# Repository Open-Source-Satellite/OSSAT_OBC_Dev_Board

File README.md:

# Open Source Satellite Development On Board Computer

## Contents
- [Background](#background)
- [Introduction to the OBC Development Board](#Introduction-to-the-OBC-Development-Board)
- [OBC Development Board Manual](#OBC-Development-Board-Manual)
- [Running the OSSAT OBC Application](#running-the-ossat-obc-application)

## Background
The key drivers for the Open Source Satellite (OSSAT) are to improve the affordability, accessibility and
sustainability of space; to address the market need for an improvement in the
price:performance point of small satellites; to stimulate the next wave of disruption
in the small satellite industry; and to enable the development of new missions,
applications and services.

Small satellites initiated the initial market
disruption by leveraging COTS parts and
processes, but it appears that the unit cost
per spacecraft cannot be reduced much
further.  
CubeSats have been critical in recent years for
lowering the barriers to entry, however they
appear to be unable to provide sufficient
robustness and mission enabling capability to
support more demanding missions.  
The goal is to develop OSSAT to fill this gap and deliver microsatellite-class
performance for a CubeSat price, even when manufacturing in low volumes. The
aim is to increase the level of integration and robustness over subsequent missions
in order to develop a single platform that is affordable for use in vLEO (very Low
Earth Orbit), LEO (Low Earth Orbit), GEO (Geosynchronous Equatorial Orbit), Lunar and
interplanetary missions.  
OSSAT will be a performant and flexible
system that KISPE Space will be able to use to implement some of its own
commercial missions; however, simply using it for KISPE Space missions will not
result in the desired increase in accessibility to the design, nor stimulate the
market.  
Making the OSSAT design open source will maximise access and achieve the wider aims of the
Programme.  

## Introduction to the OBC Development Board
### Overview
The OSSAT OBC Development board provides a convenient hardware platform that collaborators can use, to develop satellite firmware.
The board is based upon the STM32 microcontroller and includes various interfaces for connection to other satellite sub-systems. 
The board includes an STLink programmer/debugger interface to facilitate firmware development and debugging activities.
The design shares several attributes with a sister board that is being developed for a space application.
Figure 1 shows a view of the board.

Figure 1:  View of the Board
<br/>
<br/>
### Features
- STM32 Microcontroller (STM32H753ZIT)
- SRAM 4Mx16bit (8Mx8bit) CMOS Static RAM
- STLink Programming and Debug interface (with UART)
- 2x CAN Bus channels (with local 120R termination), with D-Sub (9 way sockets)
- 2x UART interface
- 8x Thermistor interface (10K Negative Temperature Coefficient)
- 31x General purpose I/O lines
- Local 3V3 regulator, operating from USB supply, via Micro-USB connector
- MCU Reset Button
- 2x push-buttons for test use
- 3x status LEDs for test use
- 2x power status LEDs
- Real-time clock

### Technical Details
#### Board Overview
Figure 2 below shows a view of the fully assembled board. There are no components on the reverse side.

Figure 2:  View of Assembled Board
<br/>   
<br/> 
The block diagram for the Schematic is shown in Figure 3.

Figure 3:  Schematic Block Diagram
<br/>   
<br/> 
#### STM32 Microcontroller (STM32H753ZIT)
The STM32 MCU includes a broad set of internal features, some of which are highlighted below:
- 32-bit Arm®-M7 core
- 2Mbyte onboard Flash
- 1Mbyte RAM
- Flexible Memory controller
- Power management
- Watchdog
- Multiple communication peripherals, including CAN, I2C, SPI, UART
- ADC
- Timers and RTC
- Large number of I/O ports
- STLink / JTAG compatibility

Full details of the MCU are available from the manufacturers data sheet and reference manual, available from the STM web site. Refer to:
- DS12117: STM32H753xl Datasheet (32-bit Arm® Cortex®-M7 480MHz MCUs, 2MB Flash, 1MB RAM, 46 com. and analogue interfaces, crypto)
- RM0433: Reference manual, STM32H742, STM32H743/753 and STM32H750 Value line advanced Arm®-based 32-bit MCUs

### Related Documents
A list of documents related to this board is provided in the Manual and is listed here. This includes diagrams, design source files, manufacturing and & test information and test firmware.
- [KS-SCH-01466 (.PDF)](https://github.com/Open-Source-Satellite/OSSAT_OBC_Dev_Board/blob/main/OSSAT%20OBC%20Dev%20Board%20Drawings/KS-SCH-01466-01%20OSSAT%20OBC%20Dev%20Board%20Schematic.pdf) OSSAT OBC Development Board Schematic (Schematic diagram)
- [KS-SCH-01466 (.sch)](https://github.com/Open-Source-Satellite/OSSAT_OBC_Dev_Board/blob/main/OSSAT%20OBC%20Dev%20Board%20Drawings/CAD%20Source%20Files/KS-SCH-01466-01%20OSSAT%20OBC%20Dev%20Board%20Schematic.sch) OSSAT OBC Development Board Schematic (Fusion 360 schematic source file, in ‘Eagle’ format)
- [KS-SCH-01466 (.lbr)](https://github.com/Open-Source-Satellite/OSSAT_OBC_Dev_Board/blob/main/OSSAT%20OBC%20Dev%20Board%20Drawings/CAD%20Source%20Files/KS-SCH-01466-01%20OSSAT_OBC_Dev_Board_Library.lbr) OSSAT OBC Dev board library (Fusion 360 Library file in ‘Eagle’ format, for parts used in the design)
- [KS-SCH-01466 (.xlsx)](https://github.com/Open-Source-Satellite/OSSAT_OBC_Dev_Board/blob/main/OSSAT%20OBC%20Dev%20Board%20Drawings/KS-SCH-01466-01%20OSSAT%20OBC%20Dev%20Brd%20BOM%20with%20Mfr%20Data.xlsx) OSSAT OBC Dev Board BOM with manufacturer data (Bill of materials for the board assembly)
- [KS-BRD-01467 (.brd)](https://github.com/Open-Source-Satellite/OSSAT_OBC_Dev_Board/blob/main/OSSAT%20OBC%20Dev%20Board%20Drawings/CAD%20Source%20Files/KS-SCH-01467%20OSSAT%20OBC%20Dev%20Board%20PCB.brd) OSSAT OBC Development Board PCB (Fusion 360 PCB source file in ‘Eagle’ format)
- [KS-BRD-01467 (.zip)](https://github.com/Open-Source-Satellite/OSSAT_OBC_Dev_Board/blob/main/OSSAT%20OBC%20Dev%20Board%20Drawings/Gerber%20Files/KS-BRD-01467-02%20OSSAT%20Sw%20Dev%20Board%20PCB_2022-12-08.zip) OSSAT OBC Dev Board PCB Manufacturing files	(Gerber file set and PnP file)
- [KS-BRD-01467 (.docx)](https://github.com/Open-Source-Satellite/OSSAT_OBC_Dev_Board/blob/main/OSSAT%20OBC%20Dev%20Board%20Drawings/KS-BRD-01467-02%20OSSAT%20OBC%20Dev%20board%20PCB%20Layer%20Stackup.docx) OSSAT OBC Dev Board Layer Stack-up (Defines the layer stack and pcb materials / thicknesses for the board)
- [KS-DOC-01526 (.docx)](https://github.com/Open-Source-Satellite/OSSAT_OBC_Dev_Board/blob/main/OSSAT%20OBC%20Dev%20Board%20Drawings/KS-DOC-01526-02%20OSSAT%20OBC%20Dev%20Board%20Verification%20Procedure.docx) OSSAT OBC Dev Board Verification Procedure	(Used to confirm board function after build)
- [KS-DOC-01529 (.docx)](https://github.com/Open-Source-Satellite/OSSAT_OBC_Dev_Board/blob/main/OSSAT%20OBC%20Dev%20Board%20Drawings/KS-DOC-01529-01%20OSSAT%20OBC%20Dev%20Board%20Build%20Document.docx) OSSAT OBC Dev Board Build Document (Build process control document)
- [KS-SOF-01541 (software)](https://github.com/Open-Source-Satellite/OSSAT_OBC_Dev_Board/releases/tag/KS-SOF-01541-01) Software to support h/w test of the OSSAT OBC dev board	(Test Software)

## OBC Development Board Manual
Document [KS-DOC-01543 is the manual](https://github.com/Open-Source-Satellite/OSSAT_OBC_Dev_Board/blob/main/KS-DOC%2001543-01%20OSSAT%20OBC%20Dev%20Board%20Manual.docx) for the board. It covers:
- Board features
- Technical details
- Building the board
- Testing the board
- Using the board

## Running the OSSAT OBC Application
Within one year of the first launch of the OSSAT, the OSSAT OBC Application software will become open source. In the interim time, in order to develop/build and run the OSSAT OBC Application, you'll need to become an OSSAT collaborator ([Click Here](https://www.opensourcesatellite.org/register/)).
If you are an OSSAT collaborator, that's great... Click [here](/OBC_CODE_README.md) to find out how to run the OSSAT OBC Application on this development board.

## Licenses
All information in this repository is licensed Open Source through the Creative Commons license:

## Get Involved
If you wish to contribute directly to the development of OSSAT, have a look at the existing Github issues and register [here](https://www.opensourcesatellite.org/register/).

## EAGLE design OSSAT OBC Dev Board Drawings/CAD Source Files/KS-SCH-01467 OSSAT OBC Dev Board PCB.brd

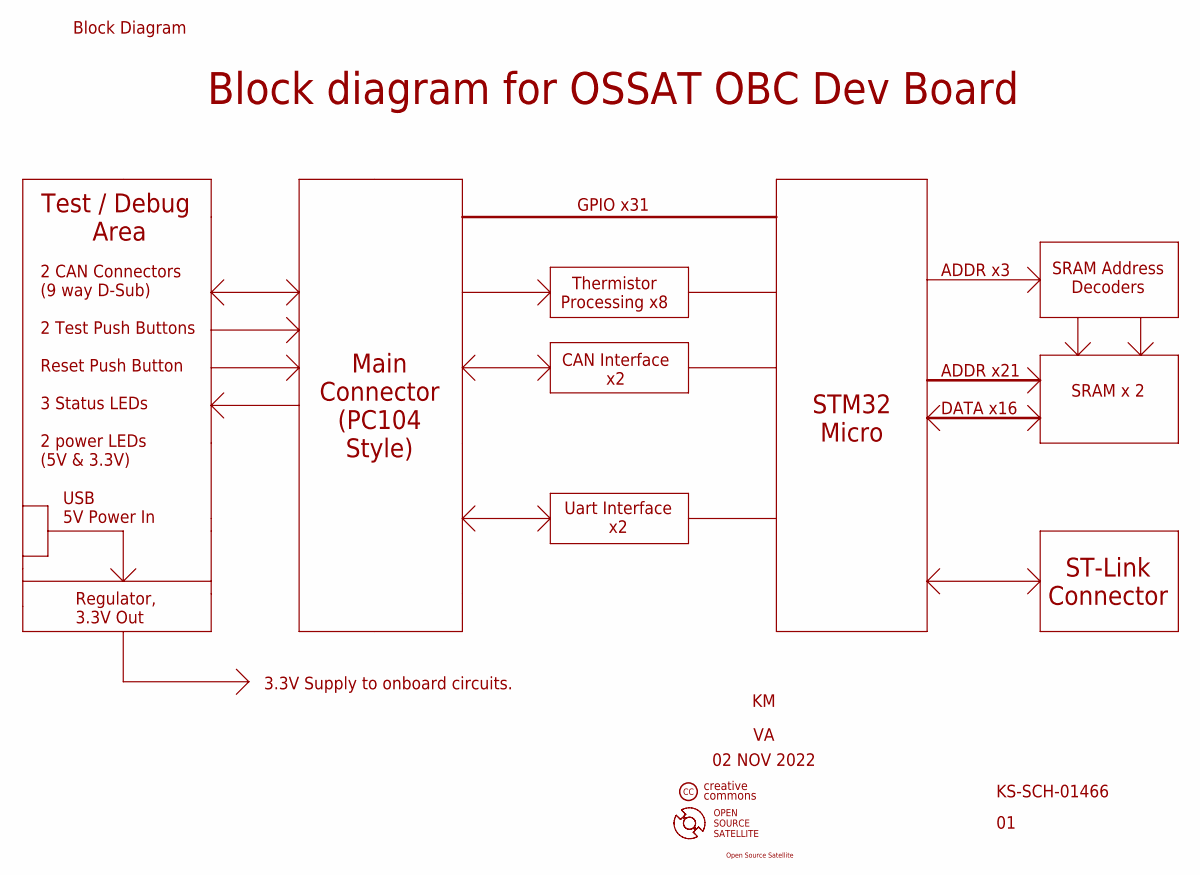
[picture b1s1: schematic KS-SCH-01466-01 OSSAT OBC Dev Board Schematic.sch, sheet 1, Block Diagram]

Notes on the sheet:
Block Diagram
Main Connector (PC104 Style)
STM32 Micro
Thermistor Processing x8
CAN Interface x2
Uart Interface x2
KS-SCH-01466
SRAM Address Decoders
SRAM x 2
ST-Link Connector
ADDR x21
DATA x16
ADDR x3
GPIO x31
Block diagram for OSSAT OBC Dev Board
02 NOV 2022
Test / Debug Area
Regulator, 3.3V Out
USB 5V Power In
3.3V Supply to onboard circuits.
2 CAN Connectors (9 way D-Sub) 2 Test Push Buttons Reset Push Button 3 Status LEDs 2 power LEDs (5V & 3.3V)
OPEN SOURCE SATELLITE
creative commons
Open Source Satellite

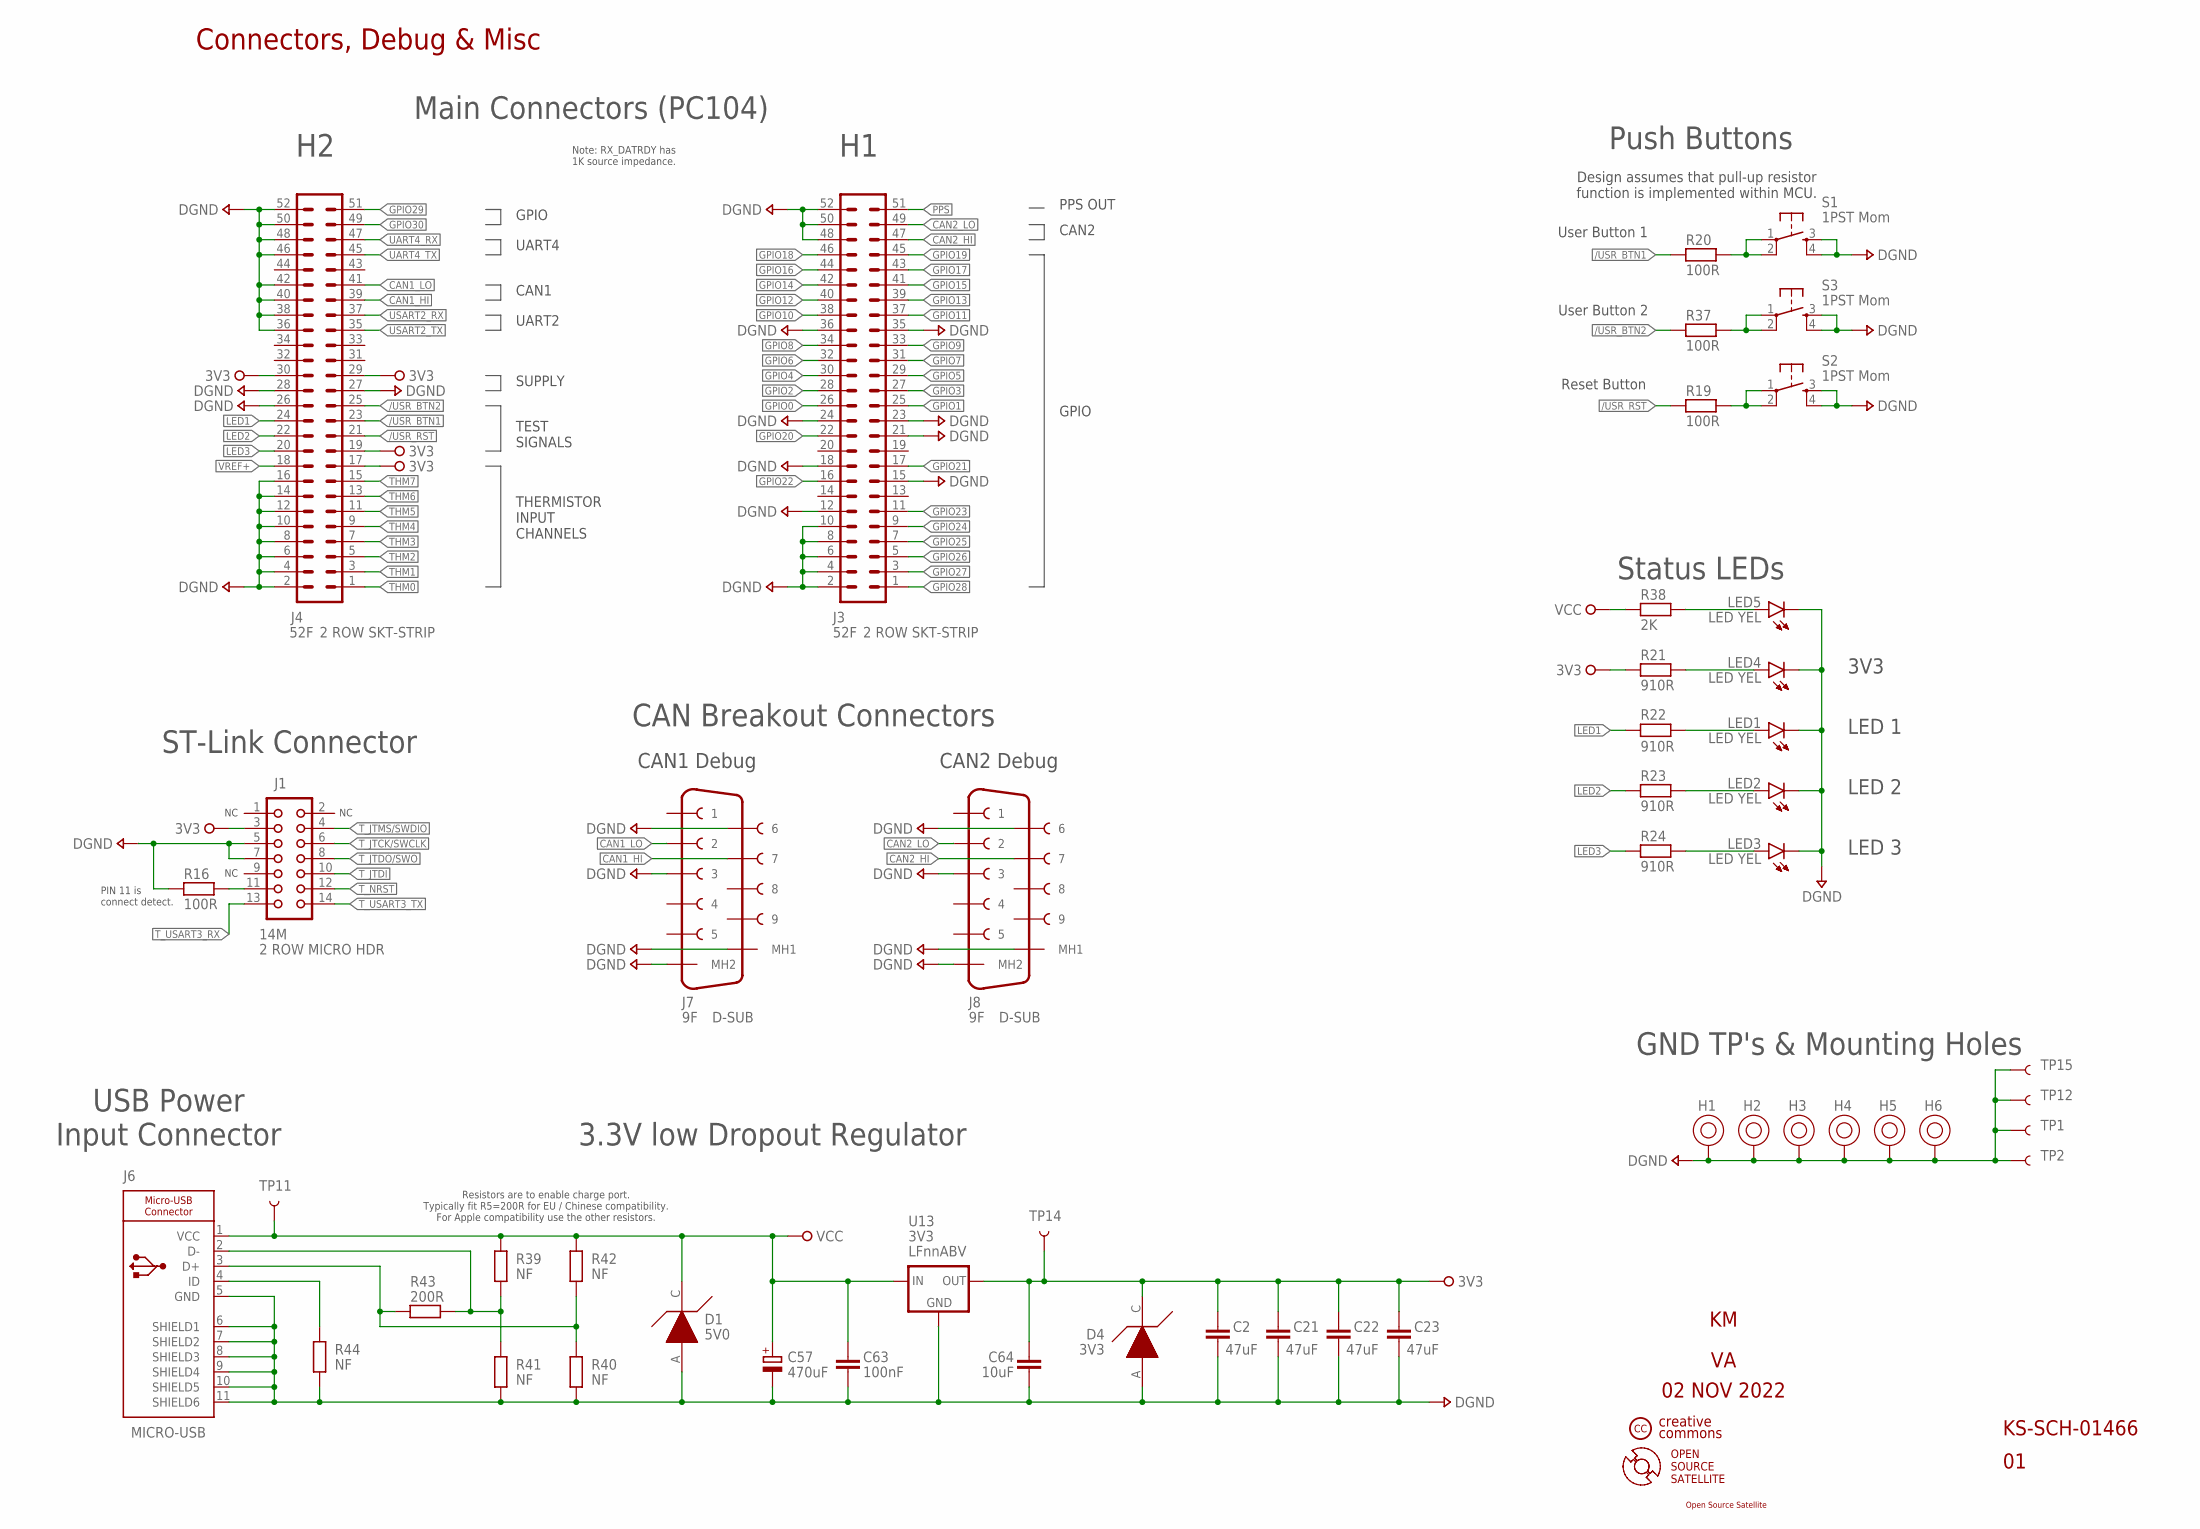
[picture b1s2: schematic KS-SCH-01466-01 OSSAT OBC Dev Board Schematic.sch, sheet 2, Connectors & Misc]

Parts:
C2, C21, C22, C23: 47uF; CAPC3225X135_1210
C57: 470uF; CAP_ELECT_RADIAL_D10_H12.5_P5
C63: 100nF; CAP_CHIP_0805
C64: 10uF; CAPC3225X135_1210
D1: 5V0; SOD323
D4: 3V3; SOD323
H1, H2, H3, H4, H5, H6: NF; HOLE-PTH-3.2-6.35
J1: 14M; HDRV14W41P127_2X7_FTSH
J3, J4: 52F; HDRVR52W64P254_2X26_6655X495X1105B
J6: CNRP105A_MICRO-USB_90DEG; CON_MICRO_USB_FEMALE
J7, J8: 9F; LD09S24A4GV00LF
LED1, LED2, LED3, LED4, LED5: OPTL102A_LED_YELLOW_0805_120DEG; LED_CHIP_0805
R16, R19, R20, R37: 100R; RES_CHIP_0805
R21, R22, R23, R24: 910R; RES_CHIP_0805
R38: 2K; RES_CHIP_0805
R39, R40, R41, R42, R44: NF; RES_CHIP_0805
R43: 200R; RES_CHIP_0805
S1, S2, S3: SWTA100A_1PST_SMD_MOMENTARY_PUSH-BUTTON; TACTILE_SWITCH_SMD_5.2MM
TP1, TP2, TP11, TP12, TP14, TP15: NF; TP-40TH
U13: 3V3; TO220L1A

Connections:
3V3: C2.1, C21.1, C22.1, C23.1, C64.1, D4.C (K), J1.3, J4.17, J4.19, J4.29, J4.30, R21.1, TP14.P$1, U13.3 (OUT); also elsewhere on the board
/USR_BTN1: J4.23, R20.2; also elsewhere on the board
/USR_BTN2: J4.25, R37.2; also elsewhere on the board
/USR_RST: J4.21, R19.2; also elsewhere on the board
CAN1_HI: J4.39, J7.7; also elsewhere on the board
CAN1_LO: J4.41, J7.2; also elsewhere on the board
CAN2_HI: J3.47, J8.7; also elsewhere on the board
CAN2_LO: J3.49, J8.2; also elsewhere on the board
DGND: C2.2, C21.2, C22.2, C23.2, C57.2 (-), C63.2, C64.2, D1.A, D4.A, H1.P$1, H2.P$1, H3.P$1, H4.P$1, H5.P$1, H6.P$1, J1.5, J1.7, J3.2, J3.4, J3.6, J3.8, J3.10, J3.12, J3.15, J3.18, J3.21, J3.23, J3.24, J3.35, J3.36, J3.48, J3.50, J3.52, J4.2, J4.4, J4.6, J4.8, J4.10, J4.12, J4.14, J4.16, J4.26, J4.27, J4.28, J4.36, J4.38, J4.40, J4.42, J4.46, J4.48, J4.50, J4.52, J6.5 (GND), J6.6 (SHIELD1), J6.7 (SHIELD2), J6.8 (SHIELD3), J6.9 (SHIELD4), J6.10 (SHIELD5), J6.11 (SHIELD6), J7.3, J7.6, J7.MH1 (MH2), J7.MH2 (MH1), J8.3, J8.6, J8.MH1 (MH2), J8.MH2 (MH1), LED1.C, LED2.C, LED3.C, LED4.C, LED5.C, R16.1, R40.1, R41.1, R44.1, S1.3, S1.4, S2.3, S2.4, S3.3, S3.4, TP1.P$1, TP2.P$1, TP12.P$1, TP15.P$1, U13.2 (GND); also elsewhere on the board
GPIO0: J3.26; also elsewhere on the board
GPIO1: J3.25; also elsewhere on the board
GPIO2: J3.28; also elsewhere on the board
GPIO3: J3.27; also elsewhere on the board
GPIO4: J3.30; also elsewhere on the board
GPIO5: J3.29; also elsewhere on the board
GPIO6: J3.32; also elsewhere on the board
GPIO7: J3.31; also elsewhere on the board
GPIO8: J3.34; also elsewhere on the board
GPIO9: J3.33; also elsewhere on the board
GPIO10: J3.38; also elsewhere on the board
GPIO11: J3.37; also elsewhere on the board
GPIO12: J3.40; also elsewhere on the board
GPIO13: J3.39; also elsewhere on the board
GPIO14: J3.42; also elsewhere on the board
GPIO15: J3.41; also elsewhere on the board
GPIO16: J3.44; also elsewhere on the board
GPIO17: J3.43; also elsewhere on the board
GPIO18: J3.46; also elsewhere on the board
GPIO19: J3.45; also elsewhere on the board
GPIO20: J3.22; also elsewhere on the board
GPIO21: J3.17; also elsewhere on the board
GPIO22: J3.16; also elsewhere on the board
GPIO23: J3.11; also elsewhere on the board
GPIO24: J3.9; also elsewhere on the board
GPIO25: J3.7; also elsewhere on the board
GPIO26: J3.5; also elsewhere on the board
GPIO27: J3.3; also elsewhere on the board
GPIO28: J3.1; also elsewhere on the board
GPIO29: J4.51; also elsewhere on the board
GPIO30: J4.49; also elsewhere on the board
LED1: J4.24, R22.1; also elsewhere on the board
LED2: J4.22, R23.1; also elsewhere on the board
LED3: J4.20, R24.1; also elsewhere on the board
unnamed: R19.1, S2.1, S2.2
unnamed: J1.11, R16.2
unnamed: R20.1, S1.1, S1.2
unnamed: LED4.A, R21.2
unnamed: LED1.A, R22.2
unnamed: LED2.A, R23.2
unnamed: LED3.A, R24.2
unnamed: R37.1, S3.1, S3.2
unnamed: LED5.A, R38.2
unnamed: J6.3 (D+), R40.2, R42.1, R43.1
unnamed: J6.2 (D-), R39.1, R41.2, R43.2
unnamed: J6.4 (ID), R44.2
PPS: J3.51; also elsewhere on the board
THM0: J4.1; also elsewhere on the board
THM1: J4.3; also elsewhere on the board
THM2: J4.5; also elsewhere on the board
THM3: J4.7; also elsewhere on the board
THM4: J4.9; also elsewhere on the board
THM5: J4.11; also elsewhere on the board
THM6: J4.13; also elsewhere on the board
THM7: J4.15; also elsewhere on the board
T_JTCK/SWCLK: J1.6; also elsewhere on the board
T_JTDI: J1.10; also elsewhere on the board
T_JTDO/SWO: J1.8; also elsewhere on the board
T_JTMS/SWDIO: J1.4; also elsewhere on the board
T_NRST: J1.12; also elsewhere on the board
T_USART3_RX: J1.13; also elsewhere on the board
T_USART3_TX: J1.14; also elsewhere on the board
UART4_RX: J4.47; also elsewhere on the board
UART4_TX: J4.45; also elsewhere on the board
USART2_RX: J4.37; also elsewhere on the board
USART2_TX: J4.35; also elsewhere on the board
VCC: C57.1 (+), C63.1, D1.C (K), J6.1 (VCC), R38.1, R39.2, R42.2, TP11.P$1, U13.1 (IN)
VREF+: J4.18; also elsewhere on the board

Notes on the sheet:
KS-SCH-01466
Connectors, Debug & Misc
ST-Link Connector
Main Connectors (PC104)
Note: RX_DATRDY has 1K source impedance.
PIN 11 is connect detect.
GND TP's & Mounting Holes
THERMISTOR INPUT CHANNELS
TEST SIGNALS
SUPPLY
CAN1
GPIO
CAN2
02 NOV 2022
CAN Breakout Connectors
CAN1 Debug
CAN2 Debug
3.3V low Dropout Regulator
Resistors are to enable charge port. Typically fit R5=200R for EU / Chinese compatibility. For Apple compatibility use the other resistors.
USB Power Input Connector
User Button 1
Reset Button
Status LEDs
3V3
LED 1
LED 2
LED 3
User Button 2
Push Buttons
Design assumes that pull-up resistor function is implemented within MCU.
UART4
UART2
PPS OUT
OPEN SOURCE SATELLITE
creative commons
Open Source Satellite

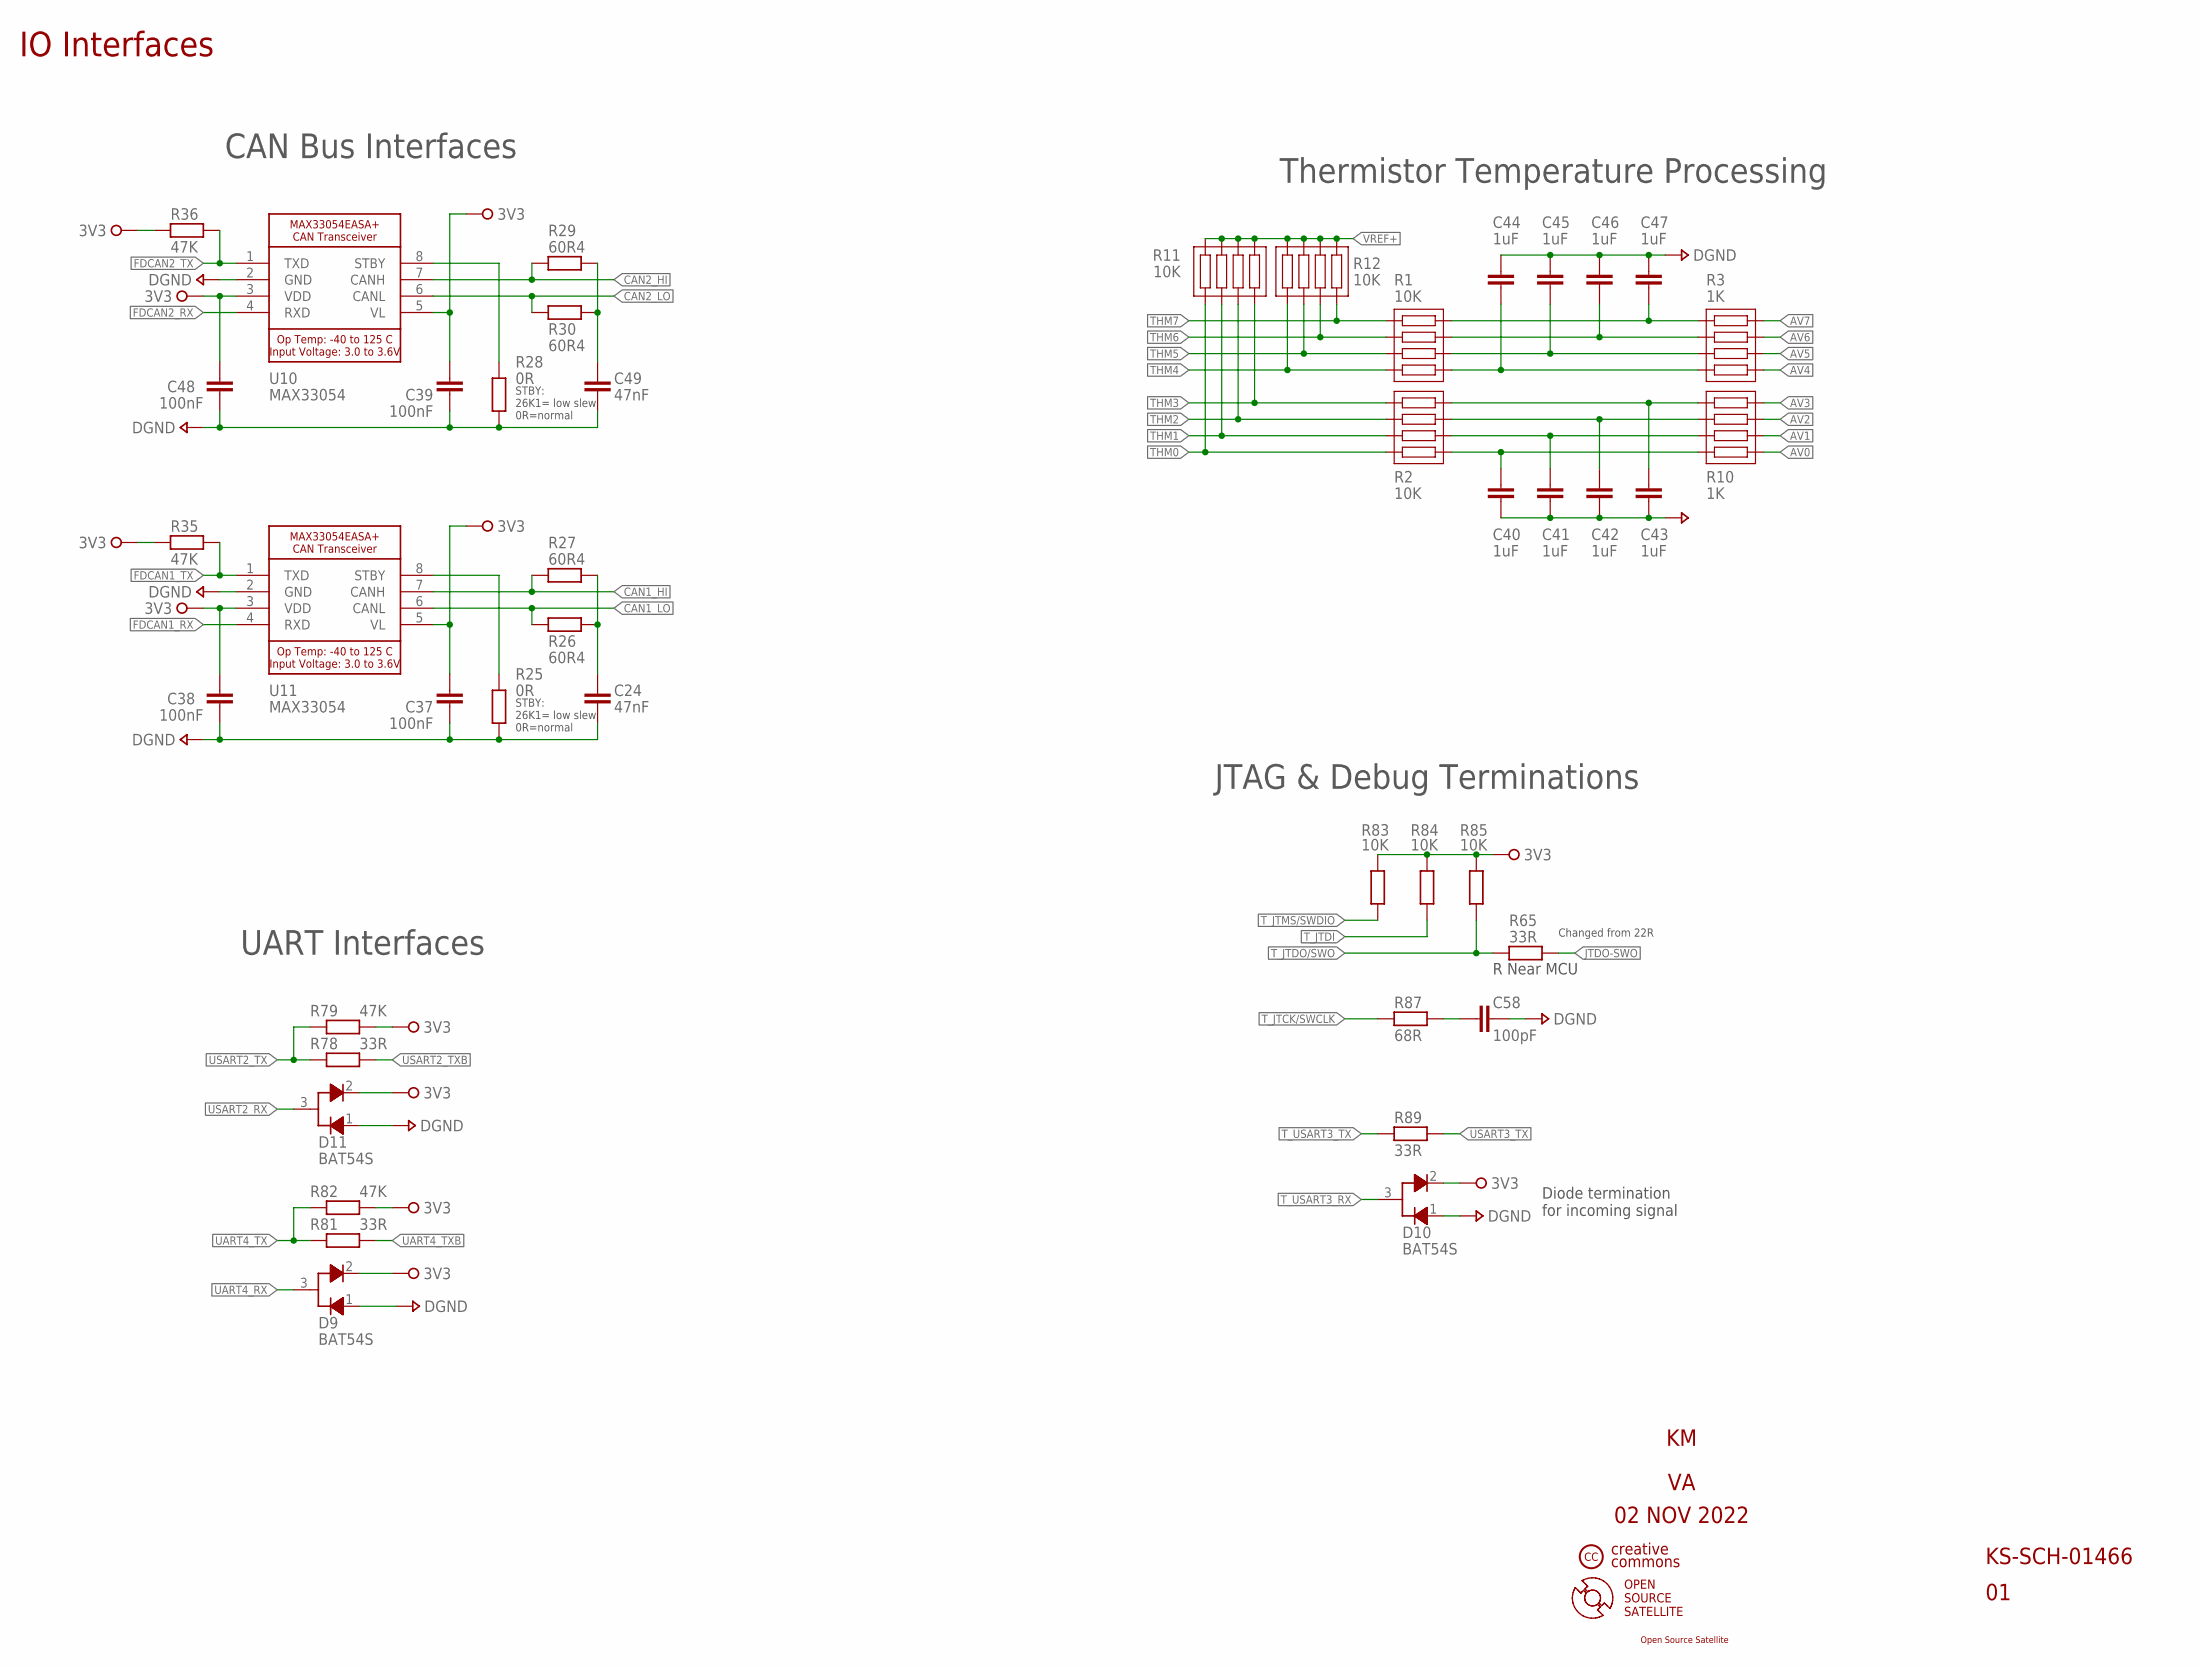
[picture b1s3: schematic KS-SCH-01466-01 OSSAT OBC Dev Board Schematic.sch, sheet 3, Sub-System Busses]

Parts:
C24, C49: 47nF; CAP_CHIP_0805
C37, C38, C39, C48: 100nF; CAP_CHIP_0805
C40, C41, C42, C43, C44, C45, C46, C47: 1uF; CAP_CHIP_0805
C58: 100pF; CAP_CHIP_0805
D9, D10, D11: DIOC100A_BAT54S_DUAL_SCHOTTKY; SOT23
R1, R2, R11, R12: 10K; RESCAXS80P320X160X60-8N
R3, R10: 1K; RESCAXS80P320X160X60-8N
R25, R28: 0R; RES_CHIP_0805
R26, R27, R29, R30: 60R4; RES_CHIP_0805
R35, R36, R79, R82: 47K; RES_CHIP_0805
R65, R78, R81, R89: 33R; RES_CHIP_0805
R83, R84, R85: 10K; RES_CHIP_0805
R87: 68R; RES_CHIP_0805
U10, U11: ICTT100A_MAX33054EASA+_CAN-TRANCEIVER; IC_MAX33054EASA+

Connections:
3V3: C37.2, C38.2, C39.2, C48.2, D9.2, D10.2, D11.2, R35.2, R36.2, R79.2, R82.2, R83.2, R84.2, R85.2, U10.3 (VDD), U10.5 (VL), U11.3 (VDD), U11.5 (VL); also elsewhere on the board
AV0: R10.5; also elsewhere on the board
AV1: R10.6; also elsewhere on the board
AV2: R10.7; also elsewhere on the board
AV3: R10.8; also elsewhere on the board
AV4: R3.5; also elsewhere on the board
AV5: R3.6; also elsewhere on the board
AV6: R3.7; also elsewhere on the board
AV7: R3.8; also elsewhere on the board
CAN1_HI: R27.1, U11.7 (CANH); also elsewhere on the board
CAN1_LO: R26.1, U11.6 (CANL); also elsewhere on the board
CAN2_HI: R29.1, U10.7 (CANH); also elsewhere on the board
CAN2_LO: R30.1, U10.6 (CANL); also elsewhere on the board
DGND: C24.1, C37.1, C38.1, C39.1, C40.2, C41.2, C42.2, C43.2, C44.1, C45.1, C46.1, C47.1, C48.1, C49.1, C58.2, D9.1, D10.1, D11.1, R25.1, R28.1, U10.2 (GND), U11.2 (GND); also elsewhere on the board
FDCAN1_RX: U11.4 (RXD); also elsewhere on the board
FDCAN1_TX: R35.1, U11.1 (TXD); also elsewhere on the board
FDCAN2_RX: U10.4 (RXD); also elsewhere on the board
FDCAN2_TX: R36.1, U10.1 (TXD); also elsewhere on the board
JTDO-SWO: R65.2; also elsewhere on the board
L_CSN+1: C40.1, R2.5, R10.4
L_CSN+10: C41.1, R2.6, R10.3
L_CSN+11: C42.1, R2.7, R10.2
L_CSN+12: C43.1, R2.8, R10.1
L_CSN+13: C44.2, R1.5, R3.4
L_CSN+14: C45.2, R1.6, R3.3
L_CSN+15: C46.2, R1.7, R3.2
L_CSN+16: C47.2, R1.8, R3.1
unnamed: C58.1, R87.2
unnamed: C24.2, R26.2, R27.2
unnamed: R25.2, U11.8 (STBY)
unnamed: R28.2, U10.8 (STBY)
unnamed: C49.2, R29.2, R30.2
THM0: R2.4, R11.5; also elsewhere on the board
THM1: R2.3, R11.6; also elsewhere on the board
THM2: R2.2, R11.7; also elsewhere on the board
THM3: R2.1, R11.8; also elsewhere on the board
THM4: R1.4, R12.5; also elsewhere on the board
THM5: R1.3, R12.6; also elsewhere on the board
THM6: R1.2, R12.7; also elsewhere on the board
THM7: R1.1, R12.8; also elsewhere on the board
T_JTCK/SWCLK: R87.1; also elsewhere on the board
T_JTDI: R84.1; also elsewhere on the board
T_JTDO/SWO: R65.1, R85.1; also elsewhere on the board
T_JTMS/SWDIO: R83.1; also elsewhere on the board
T_USART3_RX: D10.3; also elsewhere on the board
T_USART3_TX: R89.1; also elsewhere on the board
UART4_RX: D9.3; also elsewhere on the board
UART4_TX: R81.1, R82.1; also elsewhere on the board
UART4_TXB: R81.2; also elsewhere on the board
USART2_RX: D11.3; also elsewhere on the board
USART2_TX: R78.1, R79.1; also elsewhere on the board
USART2_TXB: R78.2; also elsewhere on the board
USART3_TX: R89.2; also elsewhere on the board
VREF+: R11.1, R11.2, R11.3, R11.4, R12.1, R12.2, R12.3, R12.4; also elsewhere on the board

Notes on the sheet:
IO Interfaces
STBY: 26K1= low slew 0R=normal
CAN Bus Interfaces
UART Interfaces
KS-SCH-01466
02 NOV 2022
Thermistor Temperature Processing
JTAG & Debug Terminations
R Near MCU
Diode termination for incoming signal
Changed from 22R
OPEN SOURCE SATELLITE
creative commons
Open Source Satellite

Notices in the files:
OSSAT OBC Dev Board Drawings/CAD Source Files/KS-SCH-01466-01 OSSAT OBC Dev Board Schematic.sch:
LICENSE_DATE: CC BY-SA 4.0: (2022)
parts and their libraries:
KSE-MSC: LICENSE_DATE: © 2022 All Rights Reserved
